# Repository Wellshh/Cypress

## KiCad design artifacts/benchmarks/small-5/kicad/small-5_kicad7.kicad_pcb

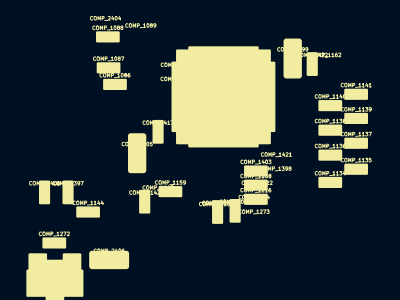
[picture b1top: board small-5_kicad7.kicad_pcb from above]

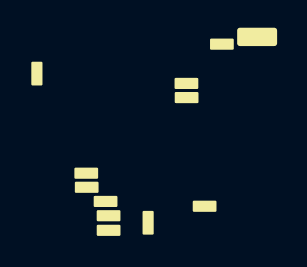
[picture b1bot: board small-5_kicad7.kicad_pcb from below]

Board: 2 copper layers, 41 parts (12 on the bottom side), 29 nets, no tracks yet.

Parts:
COMP_1076: COMP_1076; 195-0385-000
COMP_1078: COMP_1078; 195-0313-000
COMP_1086: COMP_1086; 195-3953-000
COMP_1087: COMP_1087; 195-3953-000
COMP_1088: COMP_1088; 195-3953-000
COMP_1089: COMP_1089; 195-3953-000
COMP_1134: COMP_1134; 195-0234-000
COMP_1135: COMP_1135; 195-0234-000
COMP_1136: COMP_1136; 195-0234-000
COMP_1137: COMP_1137; 195-0234-000
COMP_1138: COMP_1138; 195-0234-000
COMP_1139: COMP_1139; 195-0234-000
COMP_1140: COMP_1140; 195-0234-000
COMP_1141: COMP_1141; 195-0234-000
COMP_1142: COMP_1142; 195-0234-000
COMP_1143: COMP_1143; 195-0234-000
COMP_1144: COMP_1144; 195-0149-000
COMP_1159: COMP_1159; 195-0148-000
COMP_1162: COMP_1162; 195-3907-000
COMP_1168: COMP_1168; 195-0003-000
COMP_1216: COMP_1216; 195-0090-000
COMP_1222: COMP_1222; 195-0254-000
COMP_1250: COMP_1250; 195-0055-000
COMP_1253: COMP_1253; 195-0004-000
COMP_1272: COMP_1272; 195-2655-000
COMP_1273: COMP_1273; 195-2655-000
COMP_1397: COMP_1397; 032-0783-000
COMP_1398: COMP_1398; 032-0783-000
COMP_1403: COMP_1403; 036-0022-000
COMP_1404: COMP_1404; 036-0022-000
COMP_1406: COMP_1406; 032-1567-000
COMP_1407: COMP_1407; 032-1567-000
COMP_1417: COMP_1417; 035-0012-000
COMP_1421: COMP_1421; 032-0863-000
COMP_1422: COMP_1422; 032-0863-000
COMP_2399: COMP_2399; 032-0253-000
COMP_2404: COMP_2404; 195-1765-000
COMP_2405: COMP_2405; 195-1765-000
COMP_2406: COMP_2406; 195-1765-000
COMP_2866: COMP_2866; 316-0923-000
COMP_2927: COMP_2927; 315-0964-000

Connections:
NET_54: COMP_1088.1, COMP_1089.1, COMP_1162.2, COMP_1422.1, COMP_2399.1, COMP_2866.12
NET_537: COMP_1089.2, COMP_2866.1
NET_538: COMP_1087.2, COMP_2866.37
NET_945: COMP_1134.1, COMP_1135.1, COMP_1136.1, COMP_1137.1, COMP_1138.1, COMP_1139.1, COMP_1140.1, COMP_1141.1, COMP_1142.1, COMP_1143.1, COMP_2866.21
NET_946: COMP_1076.1, COMP_2866.26
NET_947: COMP_1272.2, COMP_1406.1, COMP_2927.1
NET_948: COMP_1159.1, COMP_2866.28
NET_949: COMP_1159.2, COMP_2866.29
NET_951: COMP_1250.2, COMP_1273.1
NET_4009: COMP_1078.1, COMP_1222.2, COMP_2866.24
NET_4226: COMP_1253.1, COMP_1407.1, COMP_2404.2, COMP_2866.40
NET_4229: COMP_1143.2, COMP_2866.27
NET_4231: COMP_1134.2, COMP_2866.20
NET_4233: COMP_1135.2, COMP_2866.19
NET_4235: COMP_1136.2, COMP_2866.18
NET_4237: COMP_1137.2, COMP_2866.17
NET_4239: COMP_1138.2, COMP_2866.16
NET_4241: COMP_1139.2, COMP_2866.15
NET_4243: COMP_1140.2, COMP_2866.14
NET_4245: COMP_1141.2, COMP_2866.13
NET_4247: COMP_1142.2, COMP_2866.30
NET_4248: COMP_1086.1, COMP_2866.36
NET_4250: COMP_1088.2, COMP_2866.38
NET_4252: COMP_1417.2, COMP_2866.32
NET_4254: COMP_1417.1, COMP_2405.1, COMP_2866.31
NET_4255: COMP_1250.1, COMP_1404.1, COMP_2866.25
NET_4280: COMP_1168.1, COMP_1216.2, COMP_1403.1, COMP_2866.22
NET_4283: COMP_1144.1, COMP_1272.1, COMP_1397.1, COMP_2406.1, COMP_2927.2
NET_4286: COMP_1087.1, COMP_1222.1, COMP_1398.1, COMP_1421.1, COMP_2866.23

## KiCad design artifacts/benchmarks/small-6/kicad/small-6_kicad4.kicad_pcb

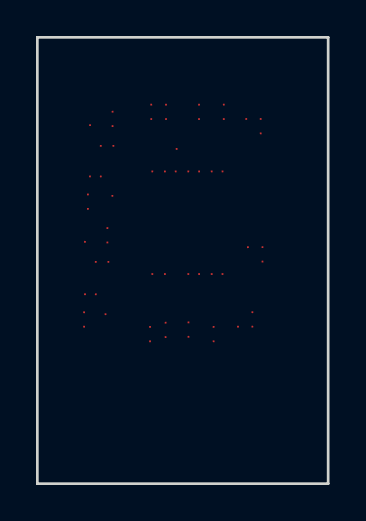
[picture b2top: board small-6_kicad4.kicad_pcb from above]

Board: 2 copper layers, 16.2 x 24.8 mm, 46 parts (0 on the bottom side), 22 nets, no tracks yet.

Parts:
C0: C0; 195-2655-000
C1: C1; 195-2655-000
C2: C2; 195-2655-000
C3: C3; 195-2655-000
C4: C4; 036-0022-000
C5: C5; 036-0022-000
C6: C6; 036-0022-000
C7: C7; 036-0022-000
C8: C8; 195-3953-000
C9: C9; 195-3953-000
C10: C10; 195-3953-000
C11: C11; 195-3953-000
C12: C12; 195-0003-000
C13: C13; 195-0003-000
C14: C14; 195-0003-000
C15: C15; 195-0003-000
C16: C16; 195-0233-000
C17: C17; 195-0233-000
C18: C18; 195-3939-000
C19: C19; 196-0045-000
C20: C20; 196-0045-000
C21: C21; 195-0090-000
C22: C22; 195-0090-000
C23: C23; 195-0035-000
C24: C24; 195-0185-000
C25: C25; 195-0185-000
C26: C26; 036-0022-000
C27: C27; 036-0022-000
C28: C28; 036-0022-000
C29: C29; 036-0022-000
C30: C30; 032-0863-000
C31: C31; 195-0295-000
C32: C32; 195-2655-000
C33: C33; 195-4010-000
C34: C34; 195-3372-000
C35: C35; 195-4010-000
C36: C36; 196-0073-000
C37: C37; 195-0151-000
C38: C38; 195-1302-000
C39: C39; 195-0364-000
C40: C40; 195-0090-000
C41: C41; 195-0295-000
C42: C42; 195-0295-000
C43: C43; 305-0058-000
C44: C44; 305-0058-000
C45: C45; 115-3132-000

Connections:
NET_5: C2.1, C6.1, C45.8
NET_35: C0.1, C4.1, C45.4
NET_39: C1.1, C5.1, C45.6
NET_49: C8.1, C9.1, C10.1, C11.1, C12.1, C13.1, C14.1, C15.1, C18.1, C19.1, C20.1, C30.1, C36.1, C45.3
NET_347: C31.2, C34.1
NET_349: C18.2, C23.2, C31.1, C45.9
NET_350: C3.2, C7.1, C45.10
NET_351: C3.1, C39.2, C40.1
NET_352: C37.2, C42.1
NET_354: C36.2, C37.1, C41.2, C45.11
NET_355: C22.1, C35.2
NET_357: C16.2, C20.2, C35.1, C45.5
NET_358: C21.1, C33.2
NET_360: C17.2, C19.2, C33.1, C45.7
NET_3926: C9.2, C43.3
NET_3927: C13.2, C27.1, C34.2, C43.5, C45.14
NET_3930: C8.2, C43.6
NET_3931: C12.2, C26.1, C42.2, C43.2, C45.13
NET_3934: C11.2, C44.3
NET_3935: C15.2, C22.2, C29.1, C44.5, C45.2
NET_3936: C10.2, C44.6
NET_3937: C14.2, C21.2, C28.1, C44.2, C45.1

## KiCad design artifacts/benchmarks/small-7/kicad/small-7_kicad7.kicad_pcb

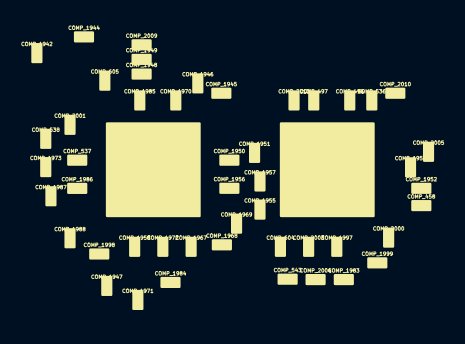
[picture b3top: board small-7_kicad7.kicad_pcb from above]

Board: 2 copper layers, 50 parts (0 on the bottom side), 44 nets, no tracks yet.

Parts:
COMP_395: COMP_395; 115-3253-000
COMP_396: COMP_396; 115-3253-000
COMP_458: COMP_458; 195-0128-000
COMP_496: COMP_496; 032-0863-000
COMP_497: COMP_497; 032-0863-000
COMP_536: COMP_536; 195-0128-000
COMP_537: COMP_537; 195-0128-000
COMP_538: COMP_538; 195-0128-000
COMP_543: COMP_543; 195-0128-000
COMP_604: COMP_604; 195-0128-000
COMP_605: COMP_605; 195-0128-000
COMP_1942: COMP_1942; 195-0005-000
COMP_1944: COMP_1944; 195-0005-000
COMP_1945: COMP_1945; 195-0128-000
COMP_1946: COMP_1946; 195-0128-000
COMP_1947: COMP_1947; 195-0128-000
COMP_1948: COMP_1948; 195-0003-000
COMP_1949: COMP_1949; 195-2655-000
COMP_1950: COMP_1950; 195-0128-000
COMP_1951: COMP_1951; 195-0128-000
COMP_1952: COMP_1952; 195-0128-000
COMP_1955: COMP_1955; 195-0128-000
COMP_1956: COMP_1956; 195-0128-000
COMP_1957: COMP_1957; 195-0128-000
COMP_1958: COMP_1958; 195-0128-000
COMP_1959: COMP_1959; 195-0128-000
COMP_1967: COMP_1967; 195-0128-000
COMP_1968: COMP_1968; 195-0128-000
COMP_1969: COMP_1969; 195-0128-000
COMP_1970: COMP_1970; 032-0863-000
COMP_1971: COMP_1971; 195-0128-000
COMP_1972: COMP_1972; 195-0128-000
COMP_1973: COMP_1973; 195-0128-000
COMP_1983: COMP_1983; 195-0128-000
COMP_1984: COMP_1984; 195-0128-000
COMP_1985: COMP_1985; 032-0863-000
COMP_1986: COMP_1986; 195-0128-000
COMP_1987: COMP_1987; 195-0128-000
COMP_1988: COMP_1988; 195-0128-000
COMP_1997: COMP_1997; 195-0128-000
COMP_1998: COMP_1998; 195-0128-000
COMP_1999: COMP_1999; 195-0128-000
COMP_2000: COMP_2000; 195-0128-000
COMP_2001: COMP_2001; 195-0128-000
COMP_2003: COMP_2003; 195-0128-000
COMP_2004: COMP_2004; 195-0128-000
COMP_2005: COMP_2005; 195-0128-000
COMP_2009: COMP_2009; 195-3953-000
COMP_2010: COMP_2010; 195-0128-000
COMP_2013: COMP_2013; 195-3953-000

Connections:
NET_45: COMP_395.27, COMP_395.31, COMP_396.27, COMP_396.31, COMP_496.1, COMP_497.1, COMP_1942.2, COMP_1944.2, COMP_1948.1, COMP_1970.1, COMP_1985.1, COMP_2013.2
NET_73: COMP_396.26, COMP_2009.2
NET_74: COMP_395.26, COMP_2013.1
NET_431: COMP_396.21, COMP_537.1
NET_452: COMP_396.22, COMP_538.1
NET_456: COMP_395.1, COMP_536.1
NET_501: COMP_395.28, COMP_396.28, COMP_1948.2, COMP_1949.2
NET_526: COMP_395.2, COMP_2010.1
NET_528: COMP_395.3, COMP_2005.1
NET_536: COMP_395.4, COMP_1959.1
NET_538: COMP_395.5, COMP_1952.1
NET_1836: COMP_395.29, COMP_396.29, COMP_1944.1
NET_1837: COMP_395.30, COMP_396.30, COMP_1942.1
NET_4122: COMP_396.15, COMP_1947.1
NET_4129: COMP_395.6, COMP_458.1
NET_4139: COMP_396.12, COMP_1972.1
NET_4163: COMP_396.11, COMP_1984.1
NET_4172: COMP_396.19, COMP_1986.1
NET_4179: COMP_396.20, COMP_1973.1
NET_4187: COMP_396.13, COMP_1971.1
NET_4196: COMP_396.14, COMP_1958.1
NET_4213: COMP_396.24, COMP_605.1
NET_4215: COMP_395.16, COMP_604.1
NET_4231: COMP_396.23, COMP_2001.1
NET_4233: COMP_395.15, COMP_543.1
NET_4244: COMP_395.13, COMP_2004.2
NET_4247: COMP_395.9, COMP_2000.1
NET_4250: COMP_395.11, COMP_1983.1
NET_4258: COMP_395.14, COMP_2003.2
NET_4261: COMP_395.10, COMP_1999.1
NET_4264: COMP_395.12, COMP_1997.1
NET_4303: COMP_396.4, COMP_1950.1
NET_4308: COMP_396.9, COMP_1968.1
NET_4313: COMP_396.5, COMP_1957.1
NET_4318: COMP_396.10, COMP_1967.1
NET_4383: COMP_396.2, COMP_1945.1
NET_4388: COMP_396.7, COMP_1955.1
NET_4393: COMP_396.3, COMP_1951.1
NET_4398: COMP_396.8, COMP_1969.1
NET_4427: COMP_396.16, COMP_1998.1
NET_4586: COMP_396.1, COMP_1946.1
NET_4591: COMP_396.6, COMP_1956.1
NET_4651: COMP_396.17, COMP_1988.1
NET_4660: COMP_396.18, COMP_1987.1

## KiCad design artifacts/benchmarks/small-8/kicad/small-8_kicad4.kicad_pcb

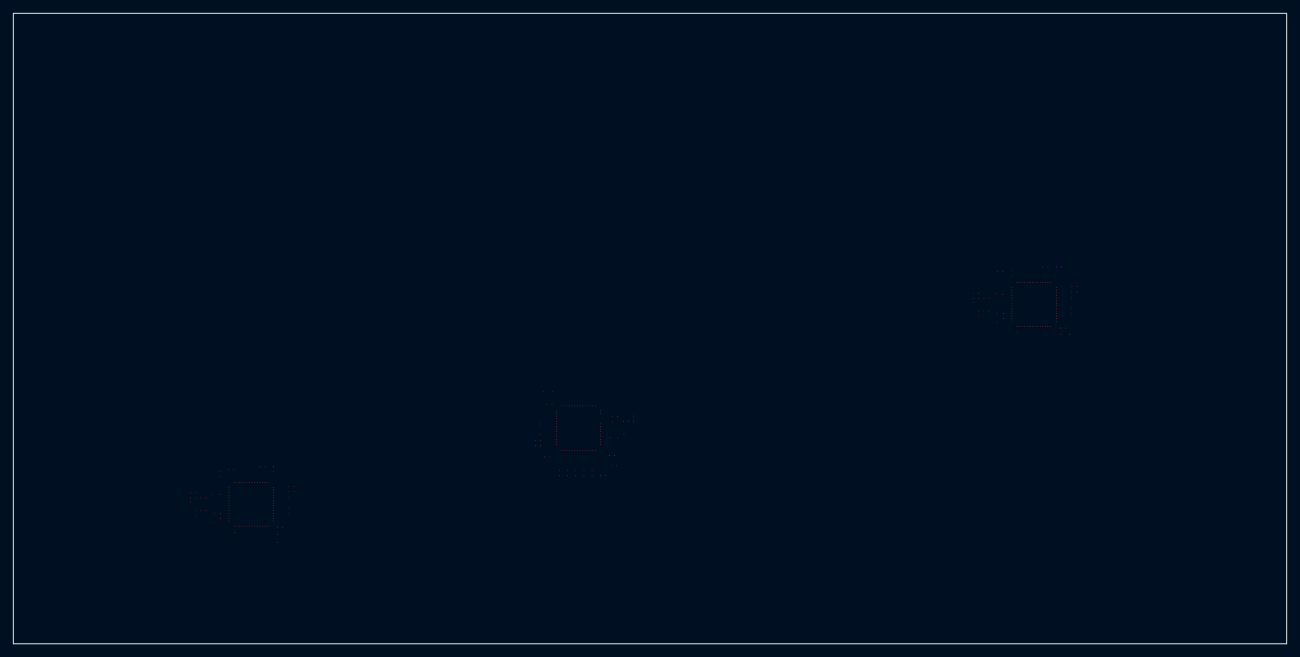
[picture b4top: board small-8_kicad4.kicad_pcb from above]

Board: 2 copper layers, 197.6 x 97.8 mm, 115 parts (0 on the bottom side), 84 nets, no tracks yet.

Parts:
C0: C0; 195-0337-000
C1: C1; 195-0089-000
C2: C2; 195-2655-000
C3: C3; 195-2655-000
C4: C4; 195-3907-000
C5: C5; 032-0863-000
C6: C6; 195-0003-000
C7: C7; 195-3953-000
C8: C8; 195-3953-000
C9: C9; 195-0090-000
C10: C10; 195-2655-000
C11: C11; 195-2655-000
C12: C12; 032-0863-000
C13: C13; 195-3953-000
C14: C14; 195-0004-000
C15: C15; 195-0004-000
C16: C16; 195-0003-000
C17: C17; 195-0254-000
C18: C18; 036-0022-000
C19: C19; 032-0863-000
C20: C20; 195-2655-000
C21: C21; 195-0004-000
C22: C22; 195-0235-000
C23: C23; 195-2655-000
C24: C24; 195-2655-000
C25: C25; 035-0012-000
C26: C26; 195-0003-000
C27: C27; 032-1567-000
C28: C28; 195-0235-000
C29: C29; 032-1567-000
C30: C30; 035-0012-000
C31: C31; 195-0004-000
C32: C32; 195-0478-000
C33: C33; 195-0254-000
C34: C34; 032-0863-000
C35: C35; 195-3907-000
C36: C36; 032-0863-000
C37: C37; 195-2655-000
C38: C38; 195-2655-000
C39: C39; 032-0863-000
C40: C40; 195-2655-000
C41: C41; 195-2655-000
C42: C42; 032-1567-000
C43: C43; 195-0235-000
C44: C44; 195-0004-000
C45: C45; 195-2655-000
C46: C46; 195-2655-000
C47: C47; 036-0022-000
C48: C48; 195-2655-000
C49: C49; 195-2655-000
C50: C50; 195-2655-000
C51: C51; 195-2655-000
C52: C52; 195-0003-000
C53: C53; 195-0090-000
C54: C54; 195-2655-000
C55: C55; 195-2655-000
C56: C56; 195-2655-000
C57: C57; 195-2655-000
C58: C58; 195-2655-000
C59: C59; 195-2655-000
C60: C60; 195-0003-000
C61: C61; 195-3953-000
C62: C62; 195-2655-000
C63: C63; 195-2655-000
C64: C64; 035-0012-000
C65: C65; 195-3953-000
C66: C66; 195-3953-000
C67: C67; 195-0004-000
C68: C68; 195-0004-000
C69: C69; 195-2655-000
C70: C70; 195-3953-000
C71: C71; 195-2655-000
C72: C72; 195-0003-000
C73: C73; 195-0004-000
C74: C74; 035-0012-000
C75: C75; 195-3953-000
C76: C76; 195-3953-000
C77: C77; 195-2655-000
C78: C78; 195-0004-000
C79: C79; 195-2655-000
C80: C80; 195-2655-000
C81: C81; 036-0022-000
C82: C82; 195-0090-000
C83: C83; 195-0003-000
C84: C84; 195-0324-000
C85: C85; 195-0254-000
C86: C86; 195-2655-000
C87: C87; 195-0003-000
C88: C88; 035-0012-000
C89: C89; 032-0863-000
C90: C90; 032-0863-000
C91: C91; 195-3907-000
C92: C92; 195-2655-000
C93: C93; 195-0235-000
C94: C94; 032-1567-000
C95: C95; 195-0004-000
C96: C96; 195-2655-000
C97: C97; 032-0863-000
C98: C98; 195-0004-000
C99: C99; 195-0235-000
C100: C100; 032-1567-000
C101: C101; 316-0885-000
C102: C102; 316-0885-000
C103: C103; 316-0885-000
C104: C104; 032-0253-000
C105: C105; 032-0253-000
C106: C106; 195-1765-000
C107: C107; 195-1765-000
C108: C108; 195-1765-000
C109: C109; 032-0253-000
C110: C110; 032-0253-000
C111: C111; 195-1765-000
C112: C112; 195-1765-000
C113: C113; 032-0253-000
C114: C114; 032-0253-000

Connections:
NET_11: C9.2, C82.2
NET_48: C4.1, C5.1, C34.1, C35.1, C91.1, C97.1
NET_49: C4.2, C7.1, C8.1, C12.1, C13.1, C103.54, C114.1
NET_51: C70.1, C75.1, C76.1, C89.1, C91.2, C101.54, C104.1
NET_53: C35.2, C39.1, C61.1, C65.1, C66.1, C102.54, C109.1
NET_83: C11.2, C103.55
NET_87: C10.2, C103.56
NET_95: C92.2, C101.55
NET_99: C86.2, C101.56
NET_101: C24.2, C103.23
NET_105: C2.2, C103.14
NET_109: C3.2, C103.13
NET_111: C77.2, C101.23
NET_115: C79.2, C101.14
NET_119: C80.2, C101.13
NET_321: C50.2, C102.5
NET_325: C49.2, C102.4
NET_329: C51.2, C102.3
NET_333: C45.2, C102.2
NET_337: C46.2, C102.1
NET_341: C37.2, C102.56
NET_345: C38.2, C102.55
NET_349: C62.2, C102.14
NET_353: C63.2, C102.13
NET_357: C59.2, C102.12
NET_361: C58.2, C102.11
NET_365: C57.2, C102.10
NET_369: C56.2, C102.9
NET_373: C55.2, C102.8
NET_377: C48.2, C102.7
NET_381: C54.2, C102.6
NET_502: C7.2, C103.17
NET_504: C75.2, C101.17
NET_542: C65.2, C102.17
NET_1812: C101.16, C102.16, C103.16
NET_1813: C101.15, C102.15, C103.15
NET_4274: C15.1, C103.20
NET_4280: C25.1, C103.46, C111.2
NET_4284: C21.1, C22.1, C29.1, C103.50
NET_4286: C20.1, C103.51
NET_4288: C78.1, C101.20
NET_4294: C88.1, C101.46, C106.2
NET_4298: C98.1, C99.1, C100.1, C101.50
NET_4300: C96.1, C101.51
NET_4302: C26.1, C103.47
NET_4304: C13.2, C103.22
NET_4305: C25.2, C103.45
NET_4312: C87.1, C101.47
NET_4314: C70.2, C101.22
NET_4315: C88.2, C101.45
NET_4342: C1.1, C17.1, C103.48
NET_4346: C9.1, C16.1, C18.1, C103.52
NET_4348: C84.1, C85.1, C101.48
NET_4352: C81.1, C82.1, C83.1, C101.52
NET_4354: C14.1, C103.21
NET_4360: C30.1, C103.27, C112.2
NET_4364: C27.1, C28.1, C31.1, C103.49
NET_4366: C23.1, C103.24
NET_4368: C73.1, C101.21
NET_4374: C74.1, C101.27, C107.2
NET_4378: C93.1, C94.1, C95.1, C101.49
NET_4380: C71.1, C101.24
NET_4382: C6.1, C103.19
NET_4384: C8.2, C103.18
NET_4385: C30.2, C103.28
NET_4392: C72.1, C101.19
NET_4394: C76.2, C101.18
NET_4395: C74.2, C101.28
NET_4583: C32.1, C33.1, C102.48
NET_4585: C60.1, C102.19
NET_4587: C66.2, C102.18
NET_4588: C64.2, C102.28
NET_4595: C68.1, C102.21
NET_4597: C67.1, C102.20
NET_4631: C61.2, C102.22
NET_4633: C64.1, C102.27, C108.2
NET_4637: C42.1, C43.1, C44.1, C102.49
NET_4639: C41.1, C102.50
NET_4641: C40.1, C102.51
NET_4643: C69.1, C102.24
NET_4647: C47.1, C52.1, C53.1, C102.52
NET_4667: C17.2, C19.1, C103.53, C113.1
NET_4669: C85.2, C90.1, C101.53, C105.1
NET_4671: C33.2, C36.1, C102.53, C110.1

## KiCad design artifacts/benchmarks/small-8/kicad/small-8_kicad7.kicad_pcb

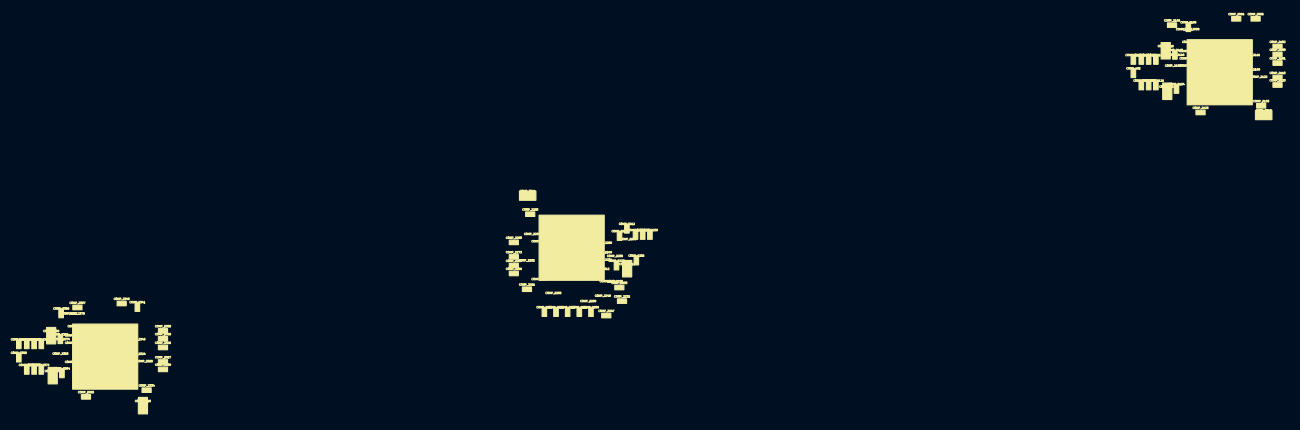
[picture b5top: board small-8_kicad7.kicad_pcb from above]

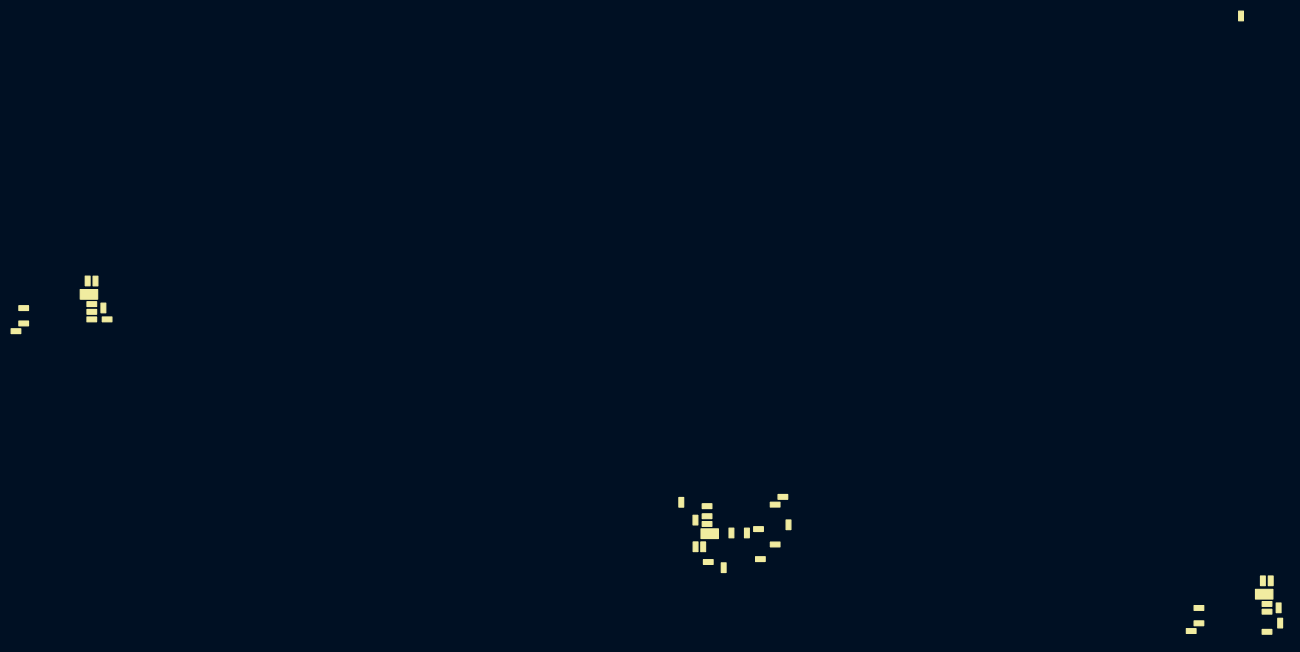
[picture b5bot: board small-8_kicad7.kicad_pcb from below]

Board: 2 copper layers, 115 parts (41 on the bottom side), 84 nets, no tracks yet.

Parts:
COMP_468: COMP_468; 195-0337-000
COMP_492: COMP_492; 195-0089-000
COMP_2095: COMP_2095; 195-2655-000
COMP_2096: COMP_2096; 195-2655-000
COMP_2097: COMP_2097; 195-3907-000
COMP_2098: COMP_2098; 032-0863-000
COMP_2101: COMP_2101; 195-0003-000
COMP_2102: COMP_2102; 195-3953-000
COMP_2103: COMP_2103; 195-3953-000
COMP_2104: COMP_2104; 195-0090-000
COMP_2105: COMP_2105; 195-2655-000
COMP_2106: COMP_2106; 195-2655-000
COMP_2107: COMP_2107; 032-0863-000
COMP_2109: COMP_2109; 195-3953-000
COMP_2110: COMP_2110; 195-0004-000
COMP_2111: COMP_2111; 195-0004-000
COMP_2112: COMP_2112; 195-0003-000
COMP_2113: COMP_2113; 195-0254-000
COMP_2114: COMP_2114; 036-0022-000
COMP_2115: COMP_2115; 032-0863-000
COMP_2116: COMP_2116; 195-2655-000
COMP_2117: COMP_2117; 195-0004-000
COMP_2118: COMP_2118; 195-0235-000
COMP_2122: COMP_2122; 195-2655-000
COMP_2123: COMP_2123; 195-2655-000
COMP_2124: COMP_2124; 035-0012-000
COMP_2125: COMP_2125; 195-0003-000
COMP_2126: COMP_2126; 032-1567-000
COMP_2127: COMP_2127; 195-0235-000
COMP_2128: COMP_2128; 032-1567-000
COMP_2130: COMP_2130; 035-0012-000
COMP_2131: COMP_2131; 195-0004-000
COMP_2212: COMP_2212; 195-0478-000
COMP_2217: COMP_2217; 195-0254-000
COMP_2225: COMP_2225; 032-0863-000
COMP_2226: COMP_2226; 195-3907-000
COMP_2227: COMP_2227; 032-0863-000
COMP_2232: COMP_2232; 195-2655-000
COMP_2233: COMP_2233; 195-2655-000
COMP_2234: COMP_2234; 032-0863-000
COMP_2235: COMP_2235; 195-2655-000
COMP_2236: COMP_2236; 195-2655-000
COMP_2237: COMP_2237; 032-1567-000
COMP_2238: COMP_2238; 195-0235-000
COMP_2239: COMP_2239; 195-0004-000
COMP_2247: COMP_2247; 195-2655-000
COMP_2248: COMP_2248; 195-2655-000
COMP_2249: COMP_2249; 036-0022-000
COMP_2255: COMP_2255; 195-2655-000
COMP_2256: COMP_2256; 195-2655-000
COMP_2257: COMP_2257; 195-2655-000
COMP_2258: COMP_2258; 195-2655-000
COMP_2259: COMP_2259; 195-0003-000
COMP_2260: COMP_2260; 195-0090-000
COMP_2261: COMP_2261; 195-2655-000
COMP_2267: COMP_2267; 195-2655-000
COMP_2268: COMP_2268; 195-2655-000
COMP_2269: COMP_2269; 195-2655-000
COMP_2271: COMP_2271; 195-2655-000
COMP_2272: COMP_2272; 195-2655-000
COMP_2273: COMP_2273; 195-0003-000
COMP_2274: COMP_2274; 195-3953-000
COMP_2281: COMP_2281; 195-2655-000
COMP_2282: COMP_2282; 195-2655-000
COMP_2283: COMP_2283; 035-0012-000
COMP_2286: COMP_2286; 195-3953-000
COMP_2287: COMP_2287; 195-3953-000
COMP_2292: COMP_2292; 195-0004-000
COMP_2293: COMP_2293; 195-0004-000
COMP_2294: COMP_2294; 195-2655-000
COMP_2324: COMP_2324; 195-3953-000
COMP_2325: COMP_2325; 195-2655-000
COMP_2326: COMP_2326; 195-0003-000
COMP_2327: COMP_2327; 195-0004-000
COMP_2334: COMP_2334; 035-0012-000
COMP_2335: COMP_2335; 195-3953-000
COMP_2336: COMP_2336; 195-3953-000
COMP_2339: COMP_2339; 195-2655-000
COMP_2340: COMP_2340; 195-0004-000
COMP_2341: COMP_2341; 195-2655-000
COMP_2345: COMP_2345; 195-2655-000
COMP_2349: COMP_2349; 036-0022-000
COMP_2350: COMP_2350; 195-0090-000
COMP_2351: COMP_2351; 195-0003-000
COMP_2355: COMP_2355; 195-0324-000
COMP_2356: COMP_2356; 195-0254-000
COMP_2357: COMP_2357; 195-2655-000
COMP_2363: COMP_2363; 195-0003-000
COMP_2364: COMP_2364; 035-0012-000
COMP_2365: COMP_2365; 032-0863-000
COMP_2366: COMP_2366; 032-0863-000
COMP_2367: COMP_2367; 195-3907-000
COMP_2368: COMP_2368; 195-2655-000
COMP_2371: COMP_2371; 195-0235-000
COMP_2372: COMP_2372; 032-1567-000
COMP_2373: COMP_2373; 195-0004-000
COMP_2374: COMP_2374; 195-2655-000
COMP_2375: COMP_2375; 032-0863-000
COMP_2380: COMP_2380; 195-0004-000
COMP_2381: COMP_2381; 195-0235-000
COMP_2382: COMP_2382; 032-1567-000
COMP_2979: COMP_2979; 316-0885-000
COMP_2980: COMP_2980; 316-0885-000
COMP_2981: COMP_2981; 316-0885-000
COMP_3307: COMP_3307; 032-0253-000
COMP_3308: COMP_3308; 032-0253-000
COMP_3309: COMP_3309; 195-1765-000
COMP_3310: COMP_3310; 195-1765-000
COMP_3311: COMP_3311; 195-1765-000
COMP_3312: COMP_3312; 032-0253-000
COMP_3313: COMP_3313; 032-0253-000
COMP_3314: COMP_3314; 195-1765-000
COMP_3315: COMP_3315; 195-1765-000
COMP_3316: COMP_3316; 032-0253-000
COMP_3317: COMP_3317; 032-0253-000

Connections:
NET_11: COMP_2104.2, COMP_2350.2
NET_48: COMP_2097.1, COMP_2098.1, COMP_2225.1, COMP_2226.1, COMP_2367.1, COMP_2375.1
NET_49: COMP_2097.2, COMP_2102.1, COMP_2103.1, COMP_2107.1, COMP_2109.1, COMP_2981.54, COMP_3317.1
NET_51: COMP_2324.1, COMP_2335.1, COMP_2336.1, COMP_2365.1, COMP_2367.2, COMP_2979.54, COMP_3307.1
NET_53: COMP_2226.2, COMP_2234.1, COMP_2274.1, COMP_2286.1, COMP_2287.1, COMP_2980.54, COMP_3312.1
NET_83: COMP_2106.2, COMP_2981.55
NET_87: COMP_2105.2, COMP_2981.56
NET_95: COMP_2368.2, COMP_2979.55
NET_99: COMP_2357.2, COMP_2979.56
NET_101: COMP_2123.2, COMP_2981.23
NET_105: COMP_2095.2, COMP_2981.14
NET_109: COMP_2096.2, COMP_2981.13
NET_111: COMP_2339.2, COMP_2979.23
NET_115: COMP_2341.2, COMP_2979.14
NET_119: COMP_2345.2, COMP_2979.13
NET_321: COMP_2257.2, COMP_2980.5
NET_325: COMP_2256.2, COMP_2980.4
NET_329: COMP_2258.2, COMP_2980.3
NET_333: COMP_2247.2, COMP_2980.2
NET_337: COMP_2248.2, COMP_2980.1
NET_341: COMP_2232.2, COMP_2980.56
NET_345: COMP_2233.2, COMP_2980.55
NET_349: COMP_2281.2, COMP_2980.14
NET_353: COMP_2282.2, COMP_2980.13
NET_357: COMP_2272.2, COMP_2980.12
NET_361: COMP_2271.2, COMP_2980.11
NET_365: COMP_2269.2, COMP_2980.10
NET_369: COMP_2268.2, COMP_2980.9
NET_373: COMP_2267.2, COMP_2980.8
NET_377: COMP_2255.2, COMP_2980.7
NET_381: COMP_2261.2, COMP_2980.6
NET_502: COMP_2102.2, COMP_2981.17
NET_504: COMP_2335.2, COMP_2979.17
NET_542: COMP_2286.2, COMP_2980.17
NET_1812: COMP_2979.16, COMP_2980.16, COMP_2981.16
NET_1813: COMP_2979.15, COMP_2980.15, COMP_2981.15
NET_4274: COMP_2111.1, COMP_2981.20
NET_4280: COMP_2124.1, COMP_2981.46, COMP_3314.2
NET_4284: COMP_2117.1, COMP_2118.1, COMP_2128.1, COMP_2981.50
NET_4286: COMP_2116.1, COMP_2981.51
NET_4288: COMP_2340.1, COMP_2979.20
NET_4294: COMP_2364.1, COMP_2979.46, COMP_3309.2
NET_4298: COMP_2380.1, COMP_2381.1, COMP_2382.1, COMP_2979.50
NET_4300: COMP_2374.1, COMP_2979.51
NET_4302: COMP_2125.1, COMP_2981.47
NET_4304: COMP_2109.2, COMP_2981.22
NET_4305: COMP_2124.2, COMP_2981.45
NET_4312: COMP_2363.1, COMP_2979.47
NET_4314: COMP_2324.2, COMP_2979.22
NET_4315: COMP_2364.2, COMP_2979.45
NET_4342: COMP_492.1, COMP_2113.1, COMP_2981.48
NET_4346: COMP_2104.1, COMP_2112.1, COMP_2114.1, COMP_2981.52
NET_4348: COMP_2355.1, COMP_2356.1, COMP_2979.48
NET_4352: COMP_2349.1, COMP_2350.1, COMP_2351.1, COMP_2979.52
NET_4354: COMP_2110.1, COMP_2981.21
NET_4360: COMP_2130.1, COMP_2981.27, COMP_3315.2
NET_4364: COMP_2126.1, COMP_2127.1, COMP_2131.1, COMP_2981.49
NET_4366: COMP_2122.1, COMP_2981.24
NET_4368: COMP_2327.1, COMP_2979.21
NET_4374: COMP_2334.1, COMP_2979.27, COMP_3310.2
NET_4378: COMP_2371.1, COMP_2372.1, COMP_2373.1, COMP_2979.49
NET_4380: COMP_2325.1, COMP_2979.24
NET_4382: COMP_2101.1, COMP_2981.19
NET_4384: COMP_2103.2, COMP_2981.18
NET_4385: COMP_2130.2, COMP_2981.28
NET_4392: COMP_2326.1, COMP_2979.19
NET_4394: COMP_2336.2, COMP_2979.18
NET_4395: COMP_2334.2, COMP_2979.28
NET_4583: COMP_2212.1, COMP_2217.1, COMP_2980.48
NET_4585: COMP_2273.1, COMP_2980.19
NET_4587: COMP_2287.2, COMP_2980.18
NET_4588: COMP_2283.2, COMP_2980.28
NET_4595: COMP_2293.1, COMP_2980.21
NET_4597: COMP_2292.1, COMP_2980.20
NET_4631: COMP_2274.2, COMP_2980.22
NET_4633: COMP_2283.1, COMP_2980.27, COMP_3311.2
NET_4637: COMP_2237.1, COMP_2238.1, COMP_2239.1, COMP_2980.49
NET_4639: COMP_2236.1, COMP_2980.50
NET_4641: COMP_2235.1, COMP_2980.51
NET_4643: COMP_2294.1, COMP_2980.24
NET_4647: COMP_2249.1, COMP_2259.1, COMP_2260.1, COMP_2980.52
NET_4667: COMP_2113.2, COMP_2115.1, COMP_2981.53, COMP_3316.1
NET_4669: COMP_2356.2, COMP_2366.1, COMP_2979.53, COMP_3308.1
NET_4671: COMP_2217.2, COMP_2227.1, COMP_2980.53, COMP_3313.1
